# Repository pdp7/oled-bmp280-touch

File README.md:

* Teensy LC with:
   * Adafruit 128x64 OLED (SPI)
   * BMP280 Temp/Pressure sensor (I2C)
   * Cap Touch Buttons 
* OSH Park shared project:
   * https://oshpark.com/shared_projects/LjXwvU4G

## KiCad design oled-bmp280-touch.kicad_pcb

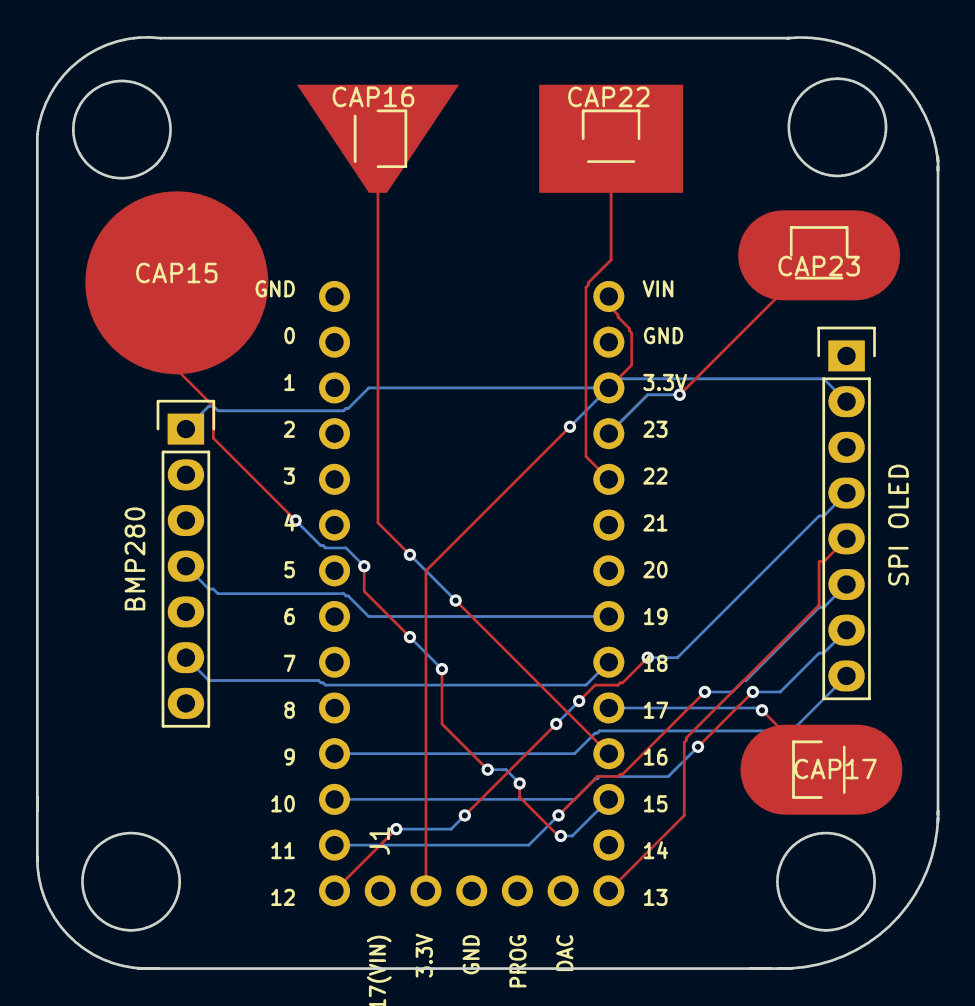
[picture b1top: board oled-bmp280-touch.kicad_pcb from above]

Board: 2 copper layers, 50.0 x 51.7 mm, 8 parts (0 on the bottom side), 14 nets.

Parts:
BMP280: I2C_BMP280; Pin_Header_Straight_1x07
CAP15: CAP15; CAPSENSE_CIRCLE_D10
CAP16: CAP16; Pin_Header_Straight_1x01
CAP17: CAP17; Pin_Header_Straight_1x01
CAP22: CAP22; Pin_Header_Straight_1x01
CAP23: CAP23; Pin_Header_Straight_1x01
J1: TEENSY-LC
SPI OLED: SPI_OLED_128x64; Pin_Header_Straight_1x08

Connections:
/D15: CAP15.1, J1.15
/D16: CAP16.1, J1.16
/D17: CAP17.1, J1.17
/D22: CAP22.1, J1.22
/D23: CAP23.1, J1.23
BMP280_SCK: BMP280.4, J1.19
BMP280_SDI: BMP280.6, J1.18
GND: BMP280.3, J1.G1, J1.G2, J1.G3, SPI OLED.1
OLED_CLK: J1.10, SPI OLED.7
OLED_CS: J1.12, SPI OLED.4
OLED_DATA: J1.9, SPI OLED.8
OLED_DC: J1.11, SPI OLED.6
OLED_RST: J1.13, SPI OLED.5
VIN: BMP280.1, J1.3V1, J1.3V2, J1.VIN, SPI OLED.2

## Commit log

2016-07-19 initial design files
2016-07-19 update layout

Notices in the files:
oled-bmp280-touch.kicad_pcb:
Released under the CERN Open Hardware License v1.2
